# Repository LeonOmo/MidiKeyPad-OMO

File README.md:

# MidiKeyPad-OMO

## What is this project?

The MidiKeypad is circuit board built around the ESP32-S3-Zero created to serve as a  pocket sized MIDI input device for sound generation.

## What does it do?

The Midi Keypad OMO is a version of Kais Midi Keypad but with a few changes. Build around the Waveshare ESP32-S3-Zero

- Microcontroller: Waveshare ESP32-S3-Zero
- Switches: For instrument choice (preset change)
- Rotary Encoder: Tempo adjustments
- Slide Potentiometers: For volume controller
- Midi Controlls: Exposed copper for note input (7 Playable Notes)

## Why does it exist?

- Just for the love of the game?: My intentions behind making this was for the pure joy i get from designing / soldering / wiring 

## Bill of Materials

| Designator | Component | LCSC Number / Link | Amount | Total Price | Description |
| :--- | :--- | :--- | :--- | :--- | :--- |
| U1 | ESP32-S3-Zero | https://www.aliexpress.com/ssr/300000512/BundleDealsDutyCovered | 1x | 5,17 € / 5,79 $ | The Brain |
| RV1-2 | Potentiometer Bourns PTA1543 Single Slide | https://de.aliexpress.com/item/1005007386348713.html| 2x | 6,10 € / 6,83 $ | Sliding Potentiometer for volume control |
| SW1-3 | Kailh Choc Low Profile Switch | https://de.aliexpress.com/item/1005011812200097.html | 3x | 7,61 € / 8,52 $ | For switching between presets / instruments |
| SW4 | EC11 Rotary Encoder | https://de.aliexpress.com/item/1005008716778661.html | 1x | 2,69 € / 3,01 $ | Used to control and adjust the tempo |
| PCB | PCB | [JLCPCB](https://jlcpcb.com/) | 1x | 4,00 $ | The PCB |
| Total Price | | 28,15 $ | | | |
| Shipping | | JLPCB 6,04 $ | | | |
| Total price with shipping | 34,19 $ | | | | |

## Tools

- PCB Design: KiCAD
- Case Design: Onshape
- Firmware: Arduino IDE (C++) (Very likely)

## Schematic

The Schematics in KiCAD

## PCB

The PCB in KiCAD

## Case

## Extra

Yes i know i should be more creative with projects like these but Kais version is just so amazing that i wanted to make a similar one. At this project, Im most proud of my PCB wiring as it is way cleaner than my lasts and you can just see where what is going where. 

## Bonus

Before i saw the Midi Keypad i wanted to make "MusicMaker!" which is probably a future project of mine. The MusicMaker! will be sort of the same but i will use a buzzer / noise output to make noise and also it will have batteries.

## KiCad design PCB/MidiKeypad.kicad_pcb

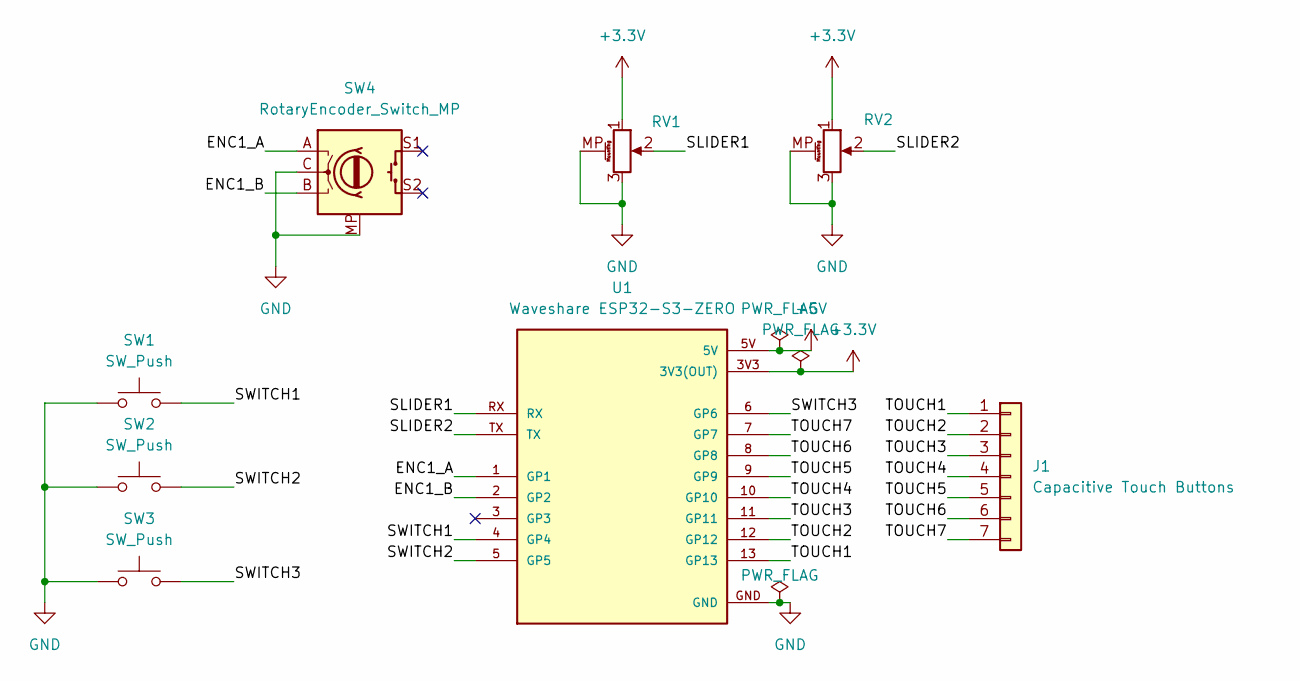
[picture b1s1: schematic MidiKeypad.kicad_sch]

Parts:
J1: Capacitive Touch Buttons; Capacitive Circles
RV1, RV2: R_Potentiometer_MountingPin; Potentiometer_Bourns_PTA1543_Single_Slide
SW1, SW2, SW3: SW_Push; Kailh Choc Low-Profile Switches
SW4: RotaryEncoder_Switch_MP; RotaryEncoder_Alps_EC12E_Vertical_H20mm
U1: Waveshare ESP32-S3-ZERO; Waveshare ESP32-S3-Zero; PARTREV NA

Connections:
+3.3V: RV1.1, RV2.1, U1.3V3 (3V3(OUT))
+5V: U1.5V
/ENC1_A: SW4.A, U1.1 (GP1)
/ENC1_B: SW4.B, U1.2 (GP2)
/SLIDER1: RV1.2, U1.RX
/SLIDER2: RV2.2, U1.TX
/SWITCH1: SW1.2, U1.4 (GP4)
/SWITCH2: SW2.2, U1.5 (GP5)
/SWITCH3: SW3.2, U1.6 (GP6)
/TOUCH1: J1.1, U1.13 (GP13)
/TOUCH2: J1.2, U1.12 (GP12)
/TOUCH3: J1.3, U1.11 (GP11)
/TOUCH4: J1.4, U1.10 (GP10)
/TOUCH5: J1.5, U1.9 (GP9)
/TOUCH6: J1.6, U1.8 (GP8)
/TOUCH7: J1.7, U1.7 (GP7)
GND: RV1.3, RV1.MP (MountPin), RV2.3, RV2.MP (MountPin), SW1.1, SW2.1, SW3.1, SW4.C, SW4.MP, U1.GND

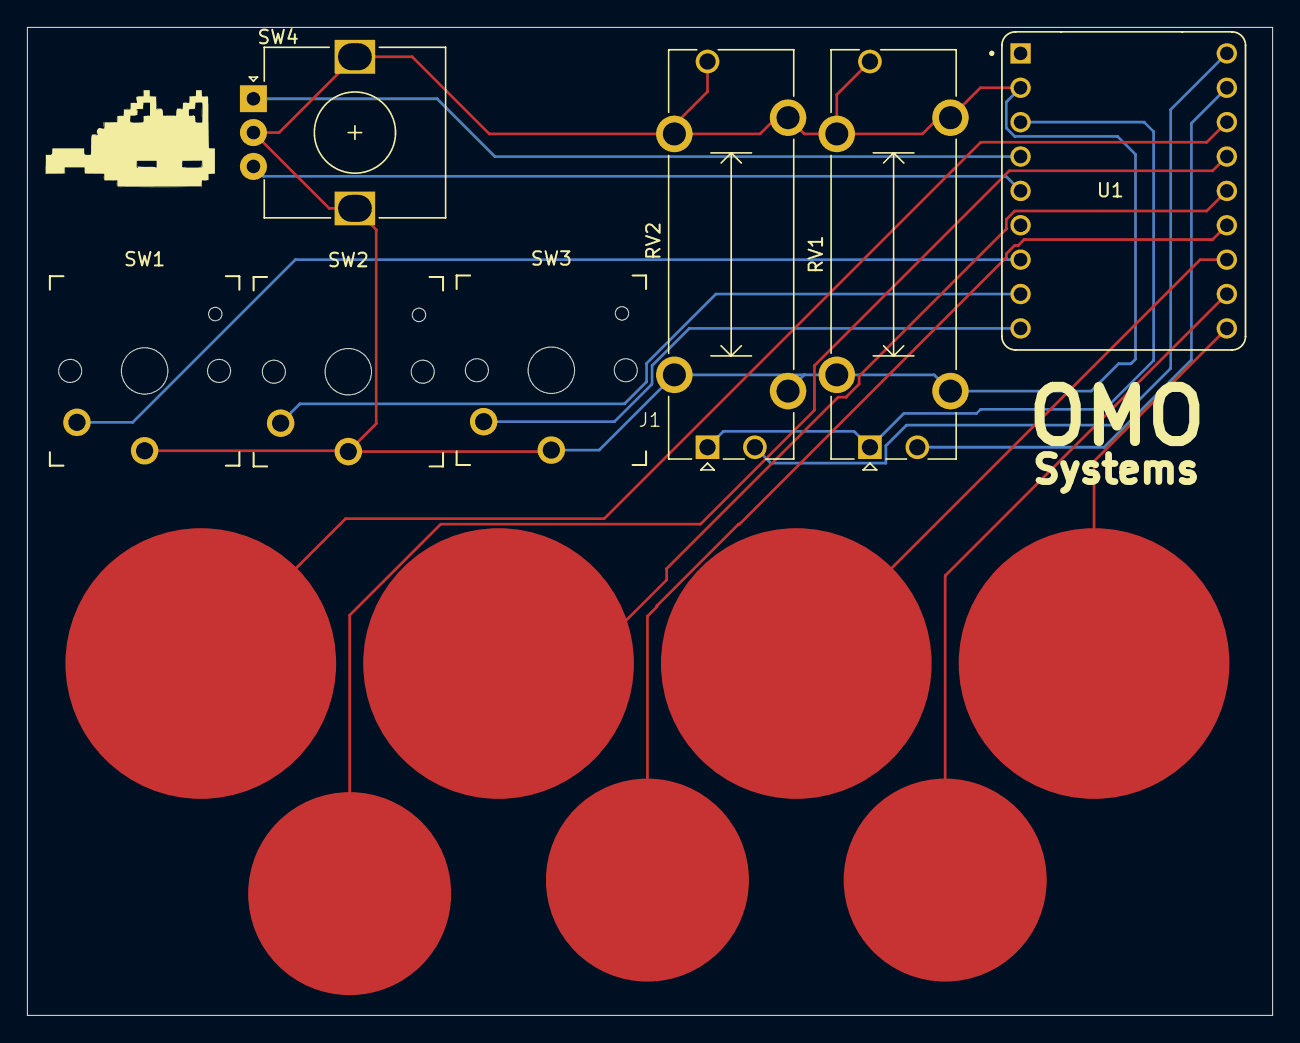
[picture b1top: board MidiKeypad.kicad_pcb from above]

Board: 2 copper layers, 92.0 x 73.0 mm, 8 parts (0 on the bottom side), 16 nets.

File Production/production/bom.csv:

Designator,Footprint,Quantity,Value,LCSC Part #
J1,Capacitive Circles,1,Capacitive Touch Buttons,
"RV1, RV2",Potentiometer_Bourns_PTA1543_Single_Slide,2,R_Potentiometer_MountingPin,
"SW1, SW2, SW3",Kailh Choc Low-Profile Switches,3,SW_Push,
SW4,RotaryEncoder_Alps_EC12E_Vertical_H20mm,1,RotaryEncoder_Switch_MP,
U1,Waveshare ESP32-S3-Zero,1,Waveshare ESP32-S3-ZERO,
